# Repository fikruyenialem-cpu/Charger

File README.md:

caution. This charger is not finishied. using it for real charger board may cause problem.

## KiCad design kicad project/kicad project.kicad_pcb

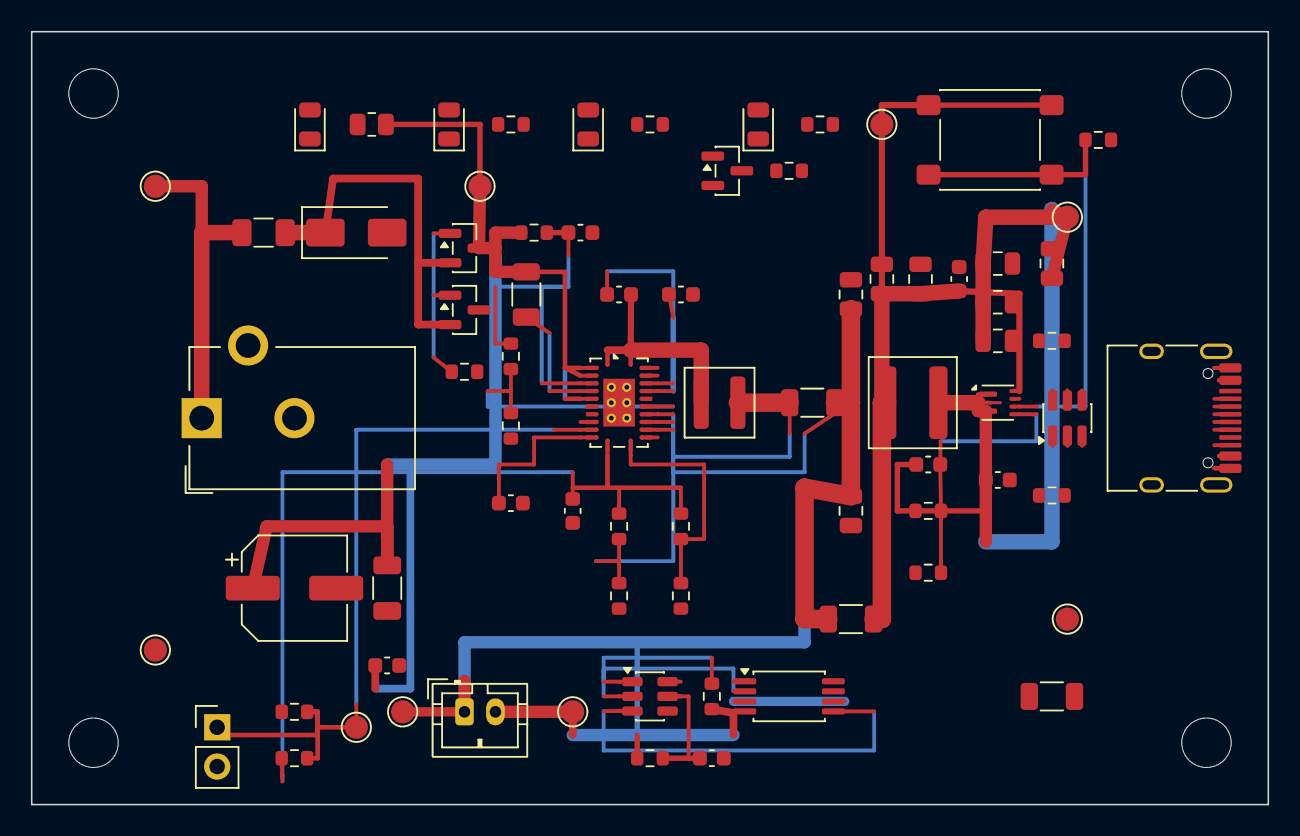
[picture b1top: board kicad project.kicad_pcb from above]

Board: 2 copper layers, 80.0 x 50.0 mm, 76 parts (0 on the bottom side), 41 nets.

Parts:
C1: CP_Elec_6.3x5.8
C2: C_1206_3216Metric
C3: C_0603_1608Metric
C_AVCC: C_0603_1608Metric
C_BOOT: C_0603_1608Metric
C_BST_IN1, C_BST_IN2: C_0805_2012Metric
C_BST_IN3: C_0603_1608Metric
C_BST_OUT1, C_BST_OUT2, C_BST_OUT3: C_0805_2012Metric
C_BST_OUT4: C_0603_1608Metric
C_FF: C_0603_1608Metric
C_OUT1, C_OUT2: C_0805_2012Metric
C_REGN: C_0603_1608Metric
C_TTC: C_0603_1608Metric
C_USB: C_0805_2012Metric
C_VDD: C_0603_1608Metric
C_VREF: C_0603_1608Metric
D1: D_SMA
D2: SOT-23
D3, D4, D5, D6: LED_0805_2012Metric
F1: Fuse_1206_3216Metric
J1: BarrelJack_CUI_PJ-102AH_Horizontal
J2: JST_PH_B2B-PH-K_1x02_P2.00mm_Vertical
J3: PinHeader_1x02_P2.54mm_Vertical
J4: USB_C_Receptacle_HRO_TYPE-C-31-M-12
L1: L_Coilcraft_XAL4030-XXX
L2: L_Coilcraft_XAL5030-XXX
Q1, Q3: SOT-23
Q2: TSSOP-8_4.4x3mm_P0.65mm
R1: R_0603_1608Metric
R_AC: R_1206_3216Metric
R_ACSET1, R_ACSET2: R_0603_1608Metric
R_AVCC: R_0603_1608Metric
R_CC1, R_CC2: R_0603_1608Metric
R_CS: R_0603_1608Metric
R_EN: R_0603_1608Metric
R_FB1, R_FB2: R_0603_1608Metric
R_ISET1, R_ISET2: R_0603_1608Metric
R_LED1: R_0805_2012Metric
R_LED2, R_LED3, R_LED4: R_0603_1608Metric
R_LINK1, R_LINK2: R_1206_3216Metric
R_OVP1, R_OVP2: R_0603_1608Metric
R_PULLUP: R_0603_1608Metric
R_SR: R_1206_3216Metric
R_TS1: R_0603_1608Metric
R_VDD: R_0603_1608Metric
SW1: SW_SPST_PTS645Sx43SMTR92
TH1: R_0603_1608Metric
TP1, TP2, TP3, TP4, TP5, TP6, TP7, TP8, TP9: TestPoint_Pad_D1.5mm
U1: Texas_RGY_R-PVQFN-N24_EP2.05x3.1mm_ThermalVias
U2, U3: SOT-23-6
U4: Texas_RWU0007A_VQFN-7_2x2mm_P0.5mm

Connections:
ACN_SENSE: R_AC.1, U1.5
ACSET_BIAS: R_ACSET1.2, R_ACSET2.1, U1.17
AVCC_CHG: C_AVCC.1, R_AVCC.1, R_OVP1.1, U1.4
BAT+: C_OUT1.1, C_OUT2.1, J2.1, R_LINK1.2, R_SR.1, R_VDD.2, TP4.1, U1.15
BAT-: J2.2, Q2.4, R_CS.1, TP5.1
BAT_NTC: J3.1, R_TS1.2, TH1.1, TP6.1, U1.10
BOOST_EN: R_EN.1, SW1.2, U4.5
BOOST_IN: C_BST_IN1.1, C_BST_IN2.1, C_BST_IN3.1, L2.2, R_LINK1.1, SW1.1, U4.7
BTST_CHG: C_BOOT.1, U1.21
CHARGE: D4.2, Q3.1, R_PULLUP.2, U1.9
CHARGE_DONE: D5.2, Q3.3
COMMON_DRAIN: Q2.3, Q2.6
CS_SENSE: R_CS.2, U2.2
DW01_VDD: C_VDD.1, R_VDD.1, U2.5
FAULT: D6.2, TP9.1
FB_BST: C_FF.2, R_FB1.2, R_FB2.1, U4.4
FUSE_OUT: D1.1, D2.2, F1.1, Q1.2
GATE_OC: Q2.5, U2.3
GATE_OD: Q2.2, U2.1
GND: C1.2, C2.2, C3.2, C_AVCC.2, C_BST_IN1.2, C_BST_IN2.2, C_BST_IN3.2, C_BST_OUT1.2, C_BST_OUT2.2, C_BST_OUT3.2, C_BST_OUT4.2, C_OUT1.2, C_OUT2.2, C_REGN.2, C_TTC.2, C_VDD.2, C_VREF.2, D1.2, D3.2, J1.2, J1.3, J3.2, Q2.1, Q3.2, R1.2, R_ACSET2.2, R_EN.2, R_FB2.2, R_ISET2.2, R_LINK2.2, R_OVP2.2, TH1.2, TP2.1, U1.14, U1.22, U1.23, U1.25, U2.6, U4.1, U4.6
ISET_BIAS: R_ISET1.2, R_ISET2.1, U1.13
LED1_A: D3.1, R_LED1.2
LED2_A: D4.1, R_LED2.2
LED3_A: D5.1, R_LED3.2
LED4_A: D6.1, R_LED4.2
OVPSET_BIAS: R_OVP1.2, R_OVP2.1, U1.18
PMOS_GATE: D2.1, Q1.1, R1.1
REGN_6V: C_REGN.1, R_LED2.1, R_LED3.1, R_LED4.1, R_PULLUP.1, U1.20
SRP_CHG: L1.1, R_SR.2, U1.16
SW_BST: L2.1, U4.2
SW_CHG: C_BOOT.2, L1.2, U1.1, U1.24
TTC_PIN: C_TTC.1, U1.11
USB_5V: C_BST_OUT1.1, C_BST_OUT2.1, C_BST_OUT3.1, C_BST_OUT4.1, C_FF.1, C_USB.1, J4.A4, J4.A9, J4.B4, J4.B9, R_CC1.1, R_CC2.1, R_FB1.1, TP7.1, U3.5, U4.3
USB_CC1: J4.A5, R_CC1.2
USB_CC2: J4.B5, R_CC2.2
USB_DN: J4.A7, J4.B7, U3.3, U3.4
USB_DP: J4.A6, J4.B6, U3.1, U3.6
USB_GND: C_USB.2, J4.A1, J4.A12, J4.B1, J4.B12, J4.SH, R_LINK2.1, TP8.1, U3.2
VIN_12V: F1.2, J1.1, TP1.1
VIN_PROTECTED: C1.1, C2.1, C3.1, Q1.3, R_AC.2, R_AVCC.2, R_LED1.1, TP3.1, U1.2, U1.3, U1.6
VREF_3V3: C_VREF.1, R_ACSET1.1, R_ISET1.1, R_TS1.1, U1.12
